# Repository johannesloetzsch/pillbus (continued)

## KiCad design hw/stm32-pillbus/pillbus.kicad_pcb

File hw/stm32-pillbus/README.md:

# PillBus

Simple and configurable bus controllers based on STM32.

## [STM32F103C8T6](https://www.lcsc.com/datasheet/lcsc_datasheet_2302211130_STMicroelectronics-STM32F103C8T6_C8734.pdf)

Different from `OtterPill`, a newer MCU is used:

* ARM Cortex-M3
* 2V~3.6V Operating Voltage Range
* 50mA max current consumption (Run mode, 72MHz, all peripherals enabled)
* 64KB Program FLASH Storage
* 20KB RAM
* max 72MHz, Internal Oscillator
* 35/37 GPIO Ports
* 2 SPI, 2 I²C, 3 USART, 1 USB 2.0 full-speed, 1 CAN
* 12bit ADC
* DMA

[MCU pinout](./pinout.md)

### Rust

Examples on similar MCUs

* [blinky-rust-nix](https://github.com/johannesloetzsch/blinky-rust-nix)
* [jamesmunns OtterPill-rs](https://github.com/jamesmunns/OtterPill-rs)
* [Tock OS](https://github.com/tock)
* [LinuxM3](http://www.linux-arm.org/LinuxKernel/LinuxM3)

## Peripherals

### [WS2812B RGB-LEDs](https://wmsc.lcsc.com/wmsc/upload/file/pdf/v2/lcsc/2406131538_XINGLIGHT-XL-5050RGBC-WS2812B-S_C22461793.pdf)

* -0.5-5.5 V Supply Voltage
* 3.0-7.0 V Logic input Voltage
* 12 mA RGB output Current

## [Power supply via USB](https://en.wikipedia.org/wiki/USB_hardware#Allowable_current_draw)

| USB Specification         | Current | Voltage | Configuration                               | usage                                      |
| ------------------------- | ------- | ------- | ------------------------------------------- | ------------------------------------------ |
| USB 2.0 Low-power device  | 100mA   | 5V      | default                                     | 1-2 MCU at max or 5 MCU at low consumption |
| USB 2.0 High-power device | 500mA   | 5V      | „Power Budgeting“ during device enumeration | 5 MCU at max + 16 RGB-LEDs                 |
| USB Battery Charging      | 1.5 A   | 5V      | charger detection algorithm                 | 5 MCU at max + 96 RGB-LEDs                 |
| USB TypeC Power Delivery  | 3.0 A   | 5V      | PD IC                                       | 5 MCU at max + ~200 RGB-LEDs               |

### [USB Battery Charging](https://usb.org/sites/default/files/BCv1.2_070312_0.zip)

`Portable Devices` „with a Good Battery“ are required to implement the charger detection algorithm defined at [Battery Charging Specification section 3.3.2](https://usb.org/sites/default/files/BCv1.2_070312_0.zip)

#### Primary Detection

`Portable Devices` (PD) are required to implement `Primary Detection` to distinguish between `Standard Downstream Port` (SDP) and different types of `Charging Ports` (`Charging Downstream Port` (SDP) or `, `Dedicated Charging Port` (DCP)).

`Dedicated Charging Ports` are identified by `RDCP_DAT <= 200 Ω` between D+ and D−. The `Portable Device` sets D+ and tests on D- if a similar voltage is detected. 

`Charging Downstream Ports` are allowed to identify by either one of two ways:
1. D- is set within `TCP_VDM_EN` of a disconnect and then unset within `TCP_VDM_DIS` of a connect.
2. D- is set exactly when `VDAT_REF < D+ < VLGC`

`Accessory charging adapters` (ACA) exist for `USB On-The-Go` and have an additional detection mechanism.

#### Secondary Detection

Secondary Detection can be used to distinguish between DCP and CDP. Portable Devices that are ready to be enumerated are allowed to bypass Secondary Detection. Secondary Detection identifies `Dedicated Charging Ports` by `RDCP_DAT <= 200 Ω` between D+ and D−. The `Portable Device` sets D- and tests on D+ if a similar voltage is detected.

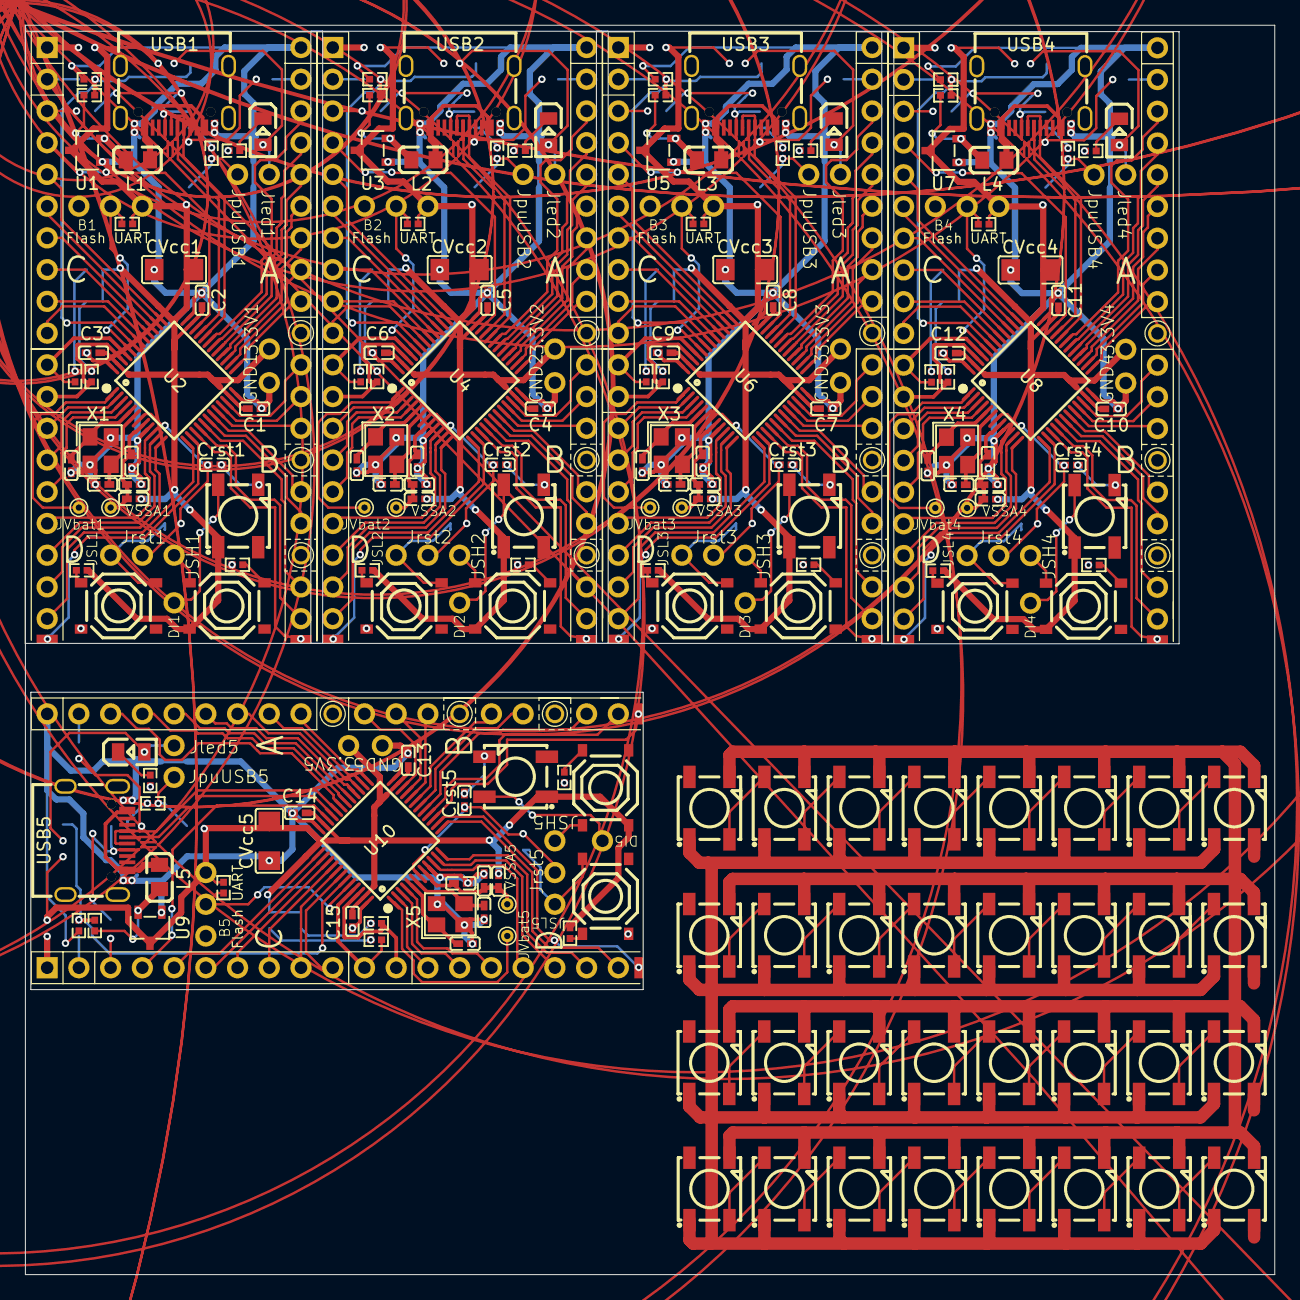
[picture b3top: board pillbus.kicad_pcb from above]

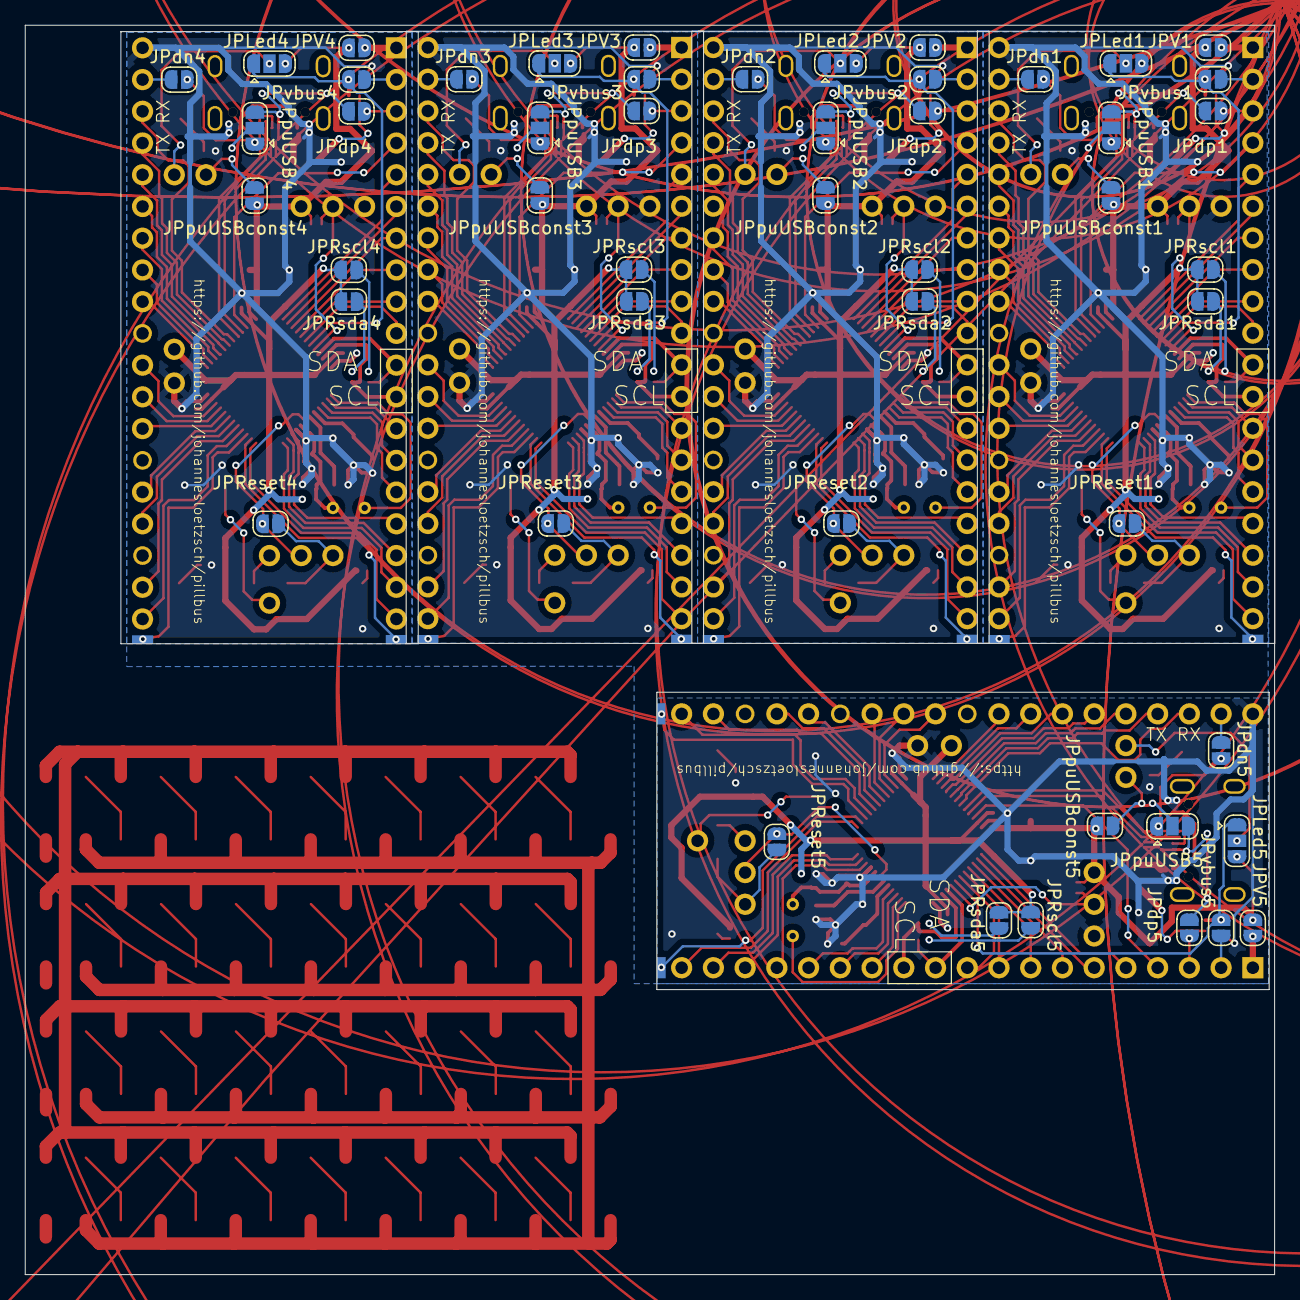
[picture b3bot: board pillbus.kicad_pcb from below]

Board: 2 copper layers, 100.0 x 100.0 mm, 297 parts (50 on the bottom side), 320 nets.

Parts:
3.3V1, 3.3V2, 3.3V3, 3.3V4, 3.3V5: PTH 1.7mm
B1, B2, B3, B4, B5: 3x PTH 1.7mm
C1, C2, C3, C4, C5, C6, C7, C8, C9, C10, C11, C12, C13, C14, C15: 100nF; C0402
CVcc1, CVcc2, CVcc3, CVcc4, CVcc5: 4.7uF; C1206
CVssA1, CVssA2, CVssA3, CVssA4, CVssA5: 1μF; C0402
CVssAn1, CVssAn2, CVssAn3, CVssAn4, CVssAn5: 10nF; C0402
Cosc1, Cosc2, Cosc3, Cosc4, Cosc5, Cosc6, Cosc7, Cosc8, Cosc9, Cosc10: 30pF; C0402
Crst1, Crst2, Crst3, Crst4, Crst5: 100nF; C0402
DI1, DI2, DI3, DI4, DI5: PTH 1.7mm
GND1, GND2, GND3, GND4, GND5: PTH 1.7mm
IDE_STM_A1, IDE_STM_A2, IDE_STM_A3, IDE_STM_A4, IDE_STM_A5: IDE STM A
IDE_STM_B1, IDE_STM_B2, IDE_STM_B3, IDE_STM_B4, IDE_STM_B5: IDE STM B cut
IDE_STM_C1, IDE_STM_C2, IDE_STM_C3, IDE_STM_C4, IDE_STM_C5: IDE STM C
IDE_STM_D1, IDE_STM_D2, IDE_STM_D3, IDE_STM_D4, IDE_STM_D5: IDE STM D cut
JPLed1, JPLed2, JPLed3, JPLed4, JPLed5: SolderJumper_3_Open; SolderJumper-3_P1.3mm_Open_RoundedPad1.0x1.5mm
JPReset1, JPReset2, JPReset3, JPReset4, JPReset5: SolderJumper_2_Open; SolderJumper-2_P1.3mm_Open_RoundedPad1.0x1.5mm
JPRscl1, JPRscl2, JPRscl3, JPRscl4, JPRscl5: SolderJumper_2_Open; SolderJumper-2_P1.3mm_Open_RoundedPad1.0x1.5mm
JPRsda1, JPRsda2, JPRsda3, JPRsda4, JPRsda5: SolderJumper_2_Open; SolderJumper-2_P1.3mm_Open_RoundedPad1.0x1.5mm
JPV1, JPV2, JPV3, JPV4, JPV5: SolderJumper_2_Open; SolderJumper-2_P1.3mm_Open_RoundedPad1.0x1.5mm
JPdn1, JPdn2, JPdn3, JPdn4, JPdn5: SolderJumper_2_Open; SolderJumper-2_P1.3mm_Open_RoundedPad1.0x1.5mm
JPdp1, JPdp2, JPdp3, JPdp4, JPdp5: SolderJumper_2_Open; SolderJumper-2_P1.3mm_Open_RoundedPad1.0x1.5mm
JPpuUSB1, JPpuUSB2, JPpuUSB3, JPpuUSB4, JPpuUSB5: SolderJumper_3_Open; SolderJumper-3_P1.3mm_Open_RoundedPad1.0x1.5mm
JPpuUSBconst1, JPpuUSBconst2, JPpuUSBconst3, JPpuUSBconst4, JPpuUSBconst5: SolderJumper_2_Open; SolderJumper-2_P1.3mm_Open_RoundedPad1.0x1.5mm
JPvbus1, JPvbus2, JPvbus3, JPvbus4, JPvbus5: SolderJumper_2_Open; SolderJumper-2_P1.3mm_Open_RoundedPad1.0x1.5mm
JSH1, JSH2, JSH3, JSH4, JSH5: PTH 1.7mm
JSL1, JSL2, JSL3, JSL4, JSL5: PTH 1.7mm
JVbat1, JVbat2, JVbat3, JVbat4, JVbat5: VBAT; TestPoint_THTPad_D1.0mm_Drill0.5mm
Jled1, Jled2, Jled3, Jled4, Jled5: PTH 1.7mm
JpuUSB1, JpuUSB2, JpuUSB3, JpuUSB4, JpuUSB5: PTH 1.7mm
Jrst1, Jrst2, Jrst3, Jrst4, Jrst5: PTH 1.7mm
L1, L2, L3, L4, L5: 100Ω@100MHz; L0805
LED1, LED2, LED3, LED4, LED5, LED6, LED7, LED8, LED9, LED10, LED11, LED12, LED13, LED14, LED15, LED16, LED17, LED18, LED19, LED20, LED21, LED22, LED23, LED24, LED25, LED26, LED27, LED28, LED29, LED30, LED31, LED32: WS2812B; LED-SMD_4P-L5.0-W5.0-TL-1
LED33, LED34, LED35, LED36, LED37: Green; LED0805-R-RD
LVssA1, LVssA2, LVssA3, LVssA4, LVssA5: 15-30nH; L0402
RGB1, RGB2, RGB3, RGB4, RGB5: LED WS2812B-S XL-5050RGBC; LED-SMD_4P-L5.0-W5.0-TL-1
RVbusI1, RVbusI2, RVbusI3, RVbusI4, RVbusI5: 51kΩ; R0402
RVbusO1, RVbusO2, RVbusO3, RVbusO4, RVbusO5: 100kΩ; R0402
Rled1, Rled2, Rled3, Rled4, Rled5: 1k-1.5k; R0402
Rpd1, Rpd2, Rpd3, Rpd4, Rpd5: 10kΩ; R0402
Rpu1, Rpu2, Rpu3, Rpu4, Rpu5: 10kΩ; R0402
RpuBoot1, RpuBoot2, RpuBoot3, RpuBoot4, RpuBoot5: 51kΩ; R0402
RpuUSB1, RpuUSB2, RpuUSB3, RpuUSB4, RpuUSB5: 1.5kΩ; R0402
Rscl1, Rscl2, Rscl3, Rscl4, Rscl5: 2.2kΩ; R0402
Rsda1, Rsda2, Rsda3, Rsda4, Rsda5: 2.2kΩ; R0402
SW1, SW2, SW3, SW4, SW5, SW6, SW7, SW8, SW9, SW10: Tactile Switch; SW-SMD_4P-L5.1-W5.1-P3.70-LS6.5-TL_H1.5
U1, U3, U5, U7, U9: 3.3V Voltage Regulator 200mA; SOT-23-3_L2.9-W1.6-P1.90-LS2.8-BR
U2, U4, U6, U8, U10: STM32F103C8T6; LQFP-48_L7.0-W7.0-P0.50-LS9.0-BL
USB1, USB2, USB3, USB4, USB5: USB_C; USB-C_SMD-TYPE-C-31-M-12
VSSA1, VSSA2, VSSA3, VSSA4, VSSA5: VSSA; TestPoint_THTPad_D1.0mm_Drill0.5mm
X1, X2, X3, X4, X5: Crystal 12MHz X322512MSB4SI; CRYSTAL-SMD_4P-L3.2-W2.5-BL

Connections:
+3.3V: 3.3V1.1, 3.3V2.1, 3.3V3.1, 3.3V4.1, 3.3V5.1, B1.3, B2.3, B3.3, B4.3, B5.3, C1.2, C2.2, C3.2, C4.2, C5.2, C6.2, C7.2, C8.2, C9.2, C10.2, C11.2, C12.2, C13.2, C14.2, C15.2, CVcc1.2, CVcc2.2, CVcc3.2, CVcc4.2, CVcc5.2, JPLed1.3 (B), JPLed2.3 (B), JPLed3.3 (B), JPLed4.3 (B), JPLed5.3 (B), JPRscl1.2 (B), JPRscl2.2 (B), JPRscl3.2 (B), JPRscl4.2 (B), JPRscl5.2 (B), JPRsda1.1 (A), JPRsda2.1 (A), JPRsda3.1 (A), JPRsda4.1 (A), JPRsda5.1 (A), JPV1.2 (B), JPV2.2 (B), JPV3.2 (B), JPV4.2 (B), JPV5.2 (B), JPpuUSBconst1.2 (B), JPpuUSBconst2.2 (B), JPpuUSBconst3.2 (B), JPpuUSBconst4.2 (B), JPpuUSBconst5.2 (B), LED1.1 (VDD), LED2.1 (VDD), LED3.1 (VDD), LED4.1 (VDD), LED5.1 (VDD), LED6.1 (VDD), LED7.1 (VDD), LED8.1 (VDD), LED9.1 (VDD), LED10.1 (VDD), LED11.1 (VDD), LED12.1 (VDD), LED13.1 (VDD), LED14.1 (VDD), LED15.1 (VDD), LED16.1 (VDD), LED17.1 (VDD), LED18.1 (VDD), LED19.1 (VDD), LED20.1 (VDD), LED21.1 (VDD), LED22.1 (VDD), LED23.1 (VDD), LED24.1 (VDD), LED25.1 (VDD), LED26.1 (VDD), LED27.1 (VDD), LED28.1 (VDD), LED29.1 (VDD), LED30.1 (VDD), LED31.1 (VDD), LED32.1 (VDD), LVssA1.2, LVssA2.2, LVssA3.2, LVssA4.2, LVssA5.2, RGB1.1 (VDD), RGB2.1 (VDD), RGB3.1 (VDD), RGB4.1 (VDD), RGB5.1 (VDD), Rpu1.2, Rpu2.2, Rpu3.2, Rpu4.2, Rpu5.2, RpuBoot1.1, RpuBoot2.1, RpuBoot3.1, RpuBoot4.1, RpuBoot5.1, SW2.2 (B), SW4.2 (B), SW6.2 (B), SW8.2 (B), SW10.2 (B), U1.3 (Vout), U2.23 (VSS_1), U2.35 (VSS_2), U2.47 (VSS_3), U3.3 (Vout), U4.23 (VSS_1), U4.35 (VSS_2), U4.47 (VSS_3), U5.3 (Vout), U6.23 (VSS_1), U6.35 (VSS_2), U6.47 (VSS_3), U7.3 (Vout), U8.23 (VSS_1), U8.35 (VSS_2), U8.47 (VSS_3), U9.3 (Vout), U10.23 (VSS_1), U10.35 (VSS_2), U10.47 (VSS_3)
/stm32pill1/Boot0: B2.2, RpuBoot2.2, U4.44 (BOOT0)
/stm32pill1/I2C1 SCL: IDE_STM_D2.SDA (IDE39_STM45), Rscl2.1, U4.45 (PB8)
/stm32pill1/I2C1 SDA: IDE_STM_D2.SCL (IDE37_STM46), Rsda2.1, U4.46 (PB9)
/stm32pill1/I2C2 SCL, USART3 TX: IDE_STM_B2.B1 (IDE24_STM13), U4.21 (PB10)
/stm32pill1/I2C2 SDA, USART3 RX: IDE_STM_B2.B0 (IDE22_STM14), U4.22 (PB11)
/stm32pill1/NRST: Crst2.2, JPReset2.1 (A), Jrst2.1, U4.7 (NRST)
/stm32pill1/OSC_IN: Cosc3.2, U4.5 (PD0-OSC_IN), X2.1 (OSC1)
/stm32pill1/OSC_OUT: Cosc4.2, U4.6 (PD1-OSC_OUT), X2.3 (OSC2)
/stm32pill1/SPI1 MISO: IDE_STM_B2.B6 (IDE38_STM3), U4.16 (PA6)
/stm32pill1/SPI1 MOSI: IDE_STM_B2.B5 (IDE36_STM4), U4.17 (PA7)
/stm32pill1/SPI1 SCK: IDE_STM_B2.B7 (IDE40_STM2), U4.15 (PA5)
/stm32pill1/SPI2 MISO: IDE_STM_A2.A5 (IDE14_STM17), U4.27 (PB14)
/stm32pill1/SPI2 MOSI: IDE_STM_A2.A4 (IDE12_STM18), U4.28 (PB15)
/stm32pill1/SPI2 NSS: IDE_STM_A2.A7 (IDE18_STM15), U4.25 (PB12)
/stm32pill1/SPI2 SCK: IDE_STM_A2.A6 (IDE16_STM16), U4.26 (PB13)
/stm32pill1/USART1 RX: IDE_STM_A2.A1 (IDE6_STM21), U4.31 (PA10)
/stm32pill1/USART1 TX: IDE_STM_A2.A2 (IDE8_STM20), U4.30 (PA9)
/stm32pill1/USB VBusSense: JPLed2.1 (A), JPvbus2.1 (A), RVbusI2.2, RVbusO2.1, U4.43 (PB7)
/stm32pill1/USBd+: JPdp2.2 (B), JPpuUSB2.3 (B), U4.33 (PA12), USB2.A6 (DP1), USB2.B6 (DP2)
/stm32pill1/USBd-: JPdn2.1 (A), JPpuUSB2.1 (A), U4.32 (PA11), USB2.A7 (DN1), USB2.B7 (DN2)
/stm32pill1/VBAT: JVbat2.1, U4.1 (VBAT)
/stm32pill1/VBUS: L2.1, RVbusI2.1, U3.2 (Vin)
/stm32pill1/VSSA: CVssA2.2, CVssAn2.2, LVssA2.1, U4.8 (VSSA), VSSA2.1
/stm32pill2/Boot0: B3.2, RpuBoot3.2, U6.44 (BOOT0)
/stm32pill2/I2C1 SCL: IDE_STM_D3.SDA (IDE39_STM45), Rscl3.1, U6.45 (PB8)
/stm32pill2/I2C1 SDA: IDE_STM_D3.SCL (IDE37_STM46), Rsda3.1, U6.46 (PB9)
/stm32pill2/I2C2 SCL, USART3 TX: IDE_STM_B3.B1 (IDE24_STM13), U6.21 (PB10)
/stm32pill2/I2C2 SDA, USART3 RX: IDE_STM_B3.B0 (IDE22_STM14), U6.22 (PB11)
/stm32pill2/NRST: Crst3.2, JPReset3.1 (A), Jrst3.1, U6.7 (NRST)
/stm32pill2/OSC_IN: Cosc5.2, U6.5 (PD0-OSC_IN), X3.1 (OSC1)
/stm32pill2/OSC_OUT: Cosc6.2, U6.6 (PD1-OSC_OUT), X3.3 (OSC2)
/stm32pill2/SPI1 MISO: IDE_STM_B3.B6 (IDE38_STM3), U6.16 (PA6)
/stm32pill2/SPI1 MOSI: IDE_STM_B3.B5 (IDE36_STM4), U6.17 (PA7)
/stm32pill2/SPI1 SCK: IDE_STM_B3.B7 (IDE40_STM2), U6.15 (PA5)
/stm32pill2/SPI2 MISO: IDE_STM_A3.A5 (IDE14_STM17), U6.27 (PB14)
/stm32pill2/SPI2 MOSI: IDE_STM_A3.A4 (IDE12_STM18), U6.28 (PB15)
/stm32pill2/SPI2 NSS: IDE_STM_A3.A7 (IDE18_STM15), U6.25 (PB12)
/stm32pill2/SPI2 SCK: IDE_STM_A3.A6 (IDE16_STM16), U6.26 (PB13)
/stm32pill2/USART1 RX: IDE_STM_A3.A1 (IDE6_STM21), U6.31 (PA10)
/stm32pill2/USART1 TX: IDE_STM_A3.A2 (IDE8_STM20), U6.30 (PA9)
/stm32pill2/USB VBusSense: JPLed3.1 (A), JPvbus3.1 (A), RVbusI3.2, RVbusO3.1, U6.43 (PB7)
/stm32pill2/USBd+: JPdp3.2 (B), JPpuUSB3.3 (B), U6.33 (PA12), USB3.A6 (DP1), USB3.B6 (DP2)
/stm32pill2/USBd-: JPdn3.1 (A), JPpuUSB3.1 (A), U6.32 (PA11), USB3.A7 (DN1), USB3.B7 (DN2)
/stm32pill2/VBAT: JVbat3.1, U6.1 (VBAT)
/stm32pill2/VBUS: L3.1, RVbusI3.1, U5.2 (Vin)
/stm32pill2/VSSA: CVssA3.2, CVssAn3.2, LVssA3.1, U6.8 (VSSA), VSSA3.1
/stm32pill3/Boot0: B4.2, RpuBoot4.2, U8.44 (BOOT0)
/stm32pill3/I2C1 SCL: IDE_STM_D4.SDA (IDE39_STM45), Rscl4.1, U8.45 (PB8)
/stm32pill3/I2C1 SDA: IDE_STM_D4.SCL (IDE37_STM46), Rsda4.1, U8.46 (PB9)
/stm32pill3/I2C2 SCL, USART3 TX: IDE_STM_B4.B1 (IDE24_STM13), U8.21 (PB10)
/stm32pill3/I2C2 SDA, USART3 RX: IDE_STM_B4.B0 (IDE22_STM14), U8.22 (PB11)
/stm32pill3/NRST: Crst4.2, JPReset4.1 (A), Jrst4.1, U8.7 (NRST)
/stm32pill3/OSC_IN: Cosc7.2, U8.5 (PD0-OSC_IN), X4.1 (OSC1)
/stm32pill3/OSC_OUT: Cosc8.2, U8.6 (PD1-OSC_OUT), X4.3 (OSC2)
/stm32pill3/SPI1 MISO: IDE_STM_B4.B6 (IDE38_STM3), U8.16 (PA6)
/stm32pill3/SPI1 MOSI: IDE_STM_B4.B5 (IDE36_STM4), U8.17 (PA7)
/stm32pill3/SPI1 SCK: IDE_STM_B4.B7 (IDE40_STM2), U8.15 (PA5)
/stm32pill3/SPI2 MISO: IDE_STM_A4.A5 (IDE14_STM17), U8.27 (PB14)
/stm32pill3/SPI2 MOSI: IDE_STM_A4.A4 (IDE12_STM18), U8.28 (PB15)
/stm32pill3/SPI2 NSS: IDE_STM_A4.A7 (IDE18_STM15), U8.25 (PB12)
/stm32pill3/SPI2 SCK: IDE_STM_A4.A6 (IDE16_STM16), U8.26 (PB13)
/stm32pill3/USART1 RX: IDE_STM_A4.A1 (IDE6_STM21), U8.31 (PA10)
/stm32pill3/USART1 TX: IDE_STM_A4.A2 (IDE8_STM20), U8.30 (PA9)
/stm32pill3/USB VBusSense: JPLed4.1 (A), JPvbus4.1 (A), RVbusI4.2, RVbusO4.1, U8.43 (PB7)
/stm32pill3/USBd+: JPdp4.2 (B), JPpuUSB4.3 (B), U8.33 (PA12), USB4.A6 (DP1), USB4.B6 (DP2)
/stm32pill3/USBd-: JPdn4.1 (A), JPpuUSB4.1 (A), U8.32 (PA11), USB4.A7 (DN1), USB4.B7 (DN2)
/stm32pill3/VBAT: JVbat4.1, U8.1 (VBAT)
/stm32pill3/VBUS: L4.1, RVbusI4.1, U7.2 (Vin)
/stm32pill3/VSSA: CVssA4.2, CVssAn4.2, LVssA4.1, U8.8 (VSSA), VSSA4.1
/stm32pill4/Boot0: B5.2, RpuBoot5.2, U10.44 (BOOT0)
/stm32pill4/I2C1 SCL: IDE_STM_D5.SDA (IDE39_STM45), Rscl5.1, U10.45 (PB8)
/stm32pill4/I2C1 SDA: IDE_STM_D5.SCL (IDE37_STM46), Rsda5.1, U10.46 (PB9)
/stm32pill4/I2C2 SCL, USART3 TX: IDE_STM_B5.B1 (IDE24_STM13), U10.21 (PB10)
/stm32pill4/I2C2 SDA, USART3 RX: IDE_STM_B5.B0 (IDE22_STM14), U10.22 (PB11)
/stm32pill4/NRST: Crst5.2, JPReset5.1 (A), Jrst5.1, U10.7 (NRST)
/stm32pill4/OSC_IN: Cosc9.2, U10.5 (PD0-OSC_IN), X5.1 (OSC1)
/stm32pill4/OSC_OUT: Cosc10.2, U10.6 (PD1-OSC_OUT), X5.3 (OSC2)
/stm32pill4/SPI1 MISO: IDE_STM_B5.B6 (IDE38_STM3), U10.16 (PA6)
/stm32pill4/SPI1 MOSI: IDE_STM_B5.B5 (IDE36_STM4), U10.17 (PA7)
/stm32pill4/SPI1 SCK: IDE_STM_B5.B7 (IDE40_STM2), U10.15 (PA5)
/stm32pill4/SPI2 MISO: IDE_STM_A5.A5 (IDE14_STM17), U10.27 (PB14)
/stm32pill4/SPI2 MOSI: IDE_STM_A5.A4 (IDE12_STM18), U10.28 (PB15)
/stm32pill4/SPI2 NSS: IDE_STM_A5.A7 (IDE18_STM15), U10.25 (PB12)
/stm32pill4/SPI2 SCK: IDE_STM_A5.A6 (IDE16_STM16), U10.26 (PB13)
/stm32pill4/USART1 RX: IDE_STM_A5.A1 (IDE6_STM21), U10.31 (PA10)
/stm32pill4/USART1 TX: IDE_STM_A5.A2 (IDE8_STM20), U10.30 (PA9)
/stm32pill4/USB VBusSense: JPLed5.1 (A), JPvbus5.1 (A), RVbusI5.2, RVbusO5.1, U10.43 (PB7)
/stm32pill4/USBd+: JPdp5.2 (B), JPpuUSB5.3 (B), U10.33 (PA12), USB5.A6 (DP1), USB5.B6 (DP2)
/stm32pill4/USBd-: JPdn5.1 (A), JPpuUSB5.1 (A), U10.32 (PA11), USB5.A7 (DN1), USB5.B7 (DN2)
/stm32pill4/VBAT: JVbat5.1, U10.1 (VBAT)
/stm32pill4/VBUS: L5.1, RVbusI5.1, U9.2 (Vin)
/stm32pill4/VSSA: CVssA5.2, CVssAn5.2, LVssA5.1, U10.8 (VSSA), VSSA5.1
/stm32pill/Boot0: B1.2, RpuBoot1.2, U2.44 (BOOT0)
/stm32pill/I2C1 SCL: IDE_STM_D1.SDA (IDE39_STM45), Rscl1.1, U2.45 (PB8)
/stm32pill/I2C1 SDA: IDE_STM_D1.SCL (IDE37_STM46), Rsda1.1, U2.46 (PB9)
/stm32pill/I2C2 SCL, USART3 TX: IDE_STM_B1.B1 (IDE24_STM13), U2.21 (PB10)
/stm32pill/I2C2 SDA, USART3 RX: IDE_STM_B1.B0 (IDE22_STM14), U2.22 (PB11)
/stm32pill/NRST: Crst1.2, JPReset1.1 (A), Jrst1.1, U2.7 (NRST)
/stm32pill/OSC_IN: Cosc1.2, U2.5 (PD0-OSC_IN), X1.1 (OSC1)
/stm32pill/OSC_OUT: Cosc2.2, U2.6 (PD1-OSC_OUT), X1.3 (OSC2)
/stm32pill/SPI1 MISO: IDE_STM_B1.B6 (IDE38_STM3), U2.16 (PA6)
/stm32pill/SPI1 MOSI: IDE_STM_B1.B5 (IDE36_STM4), U2.17 (PA7)
/stm32pill/SPI1 SCK: IDE_STM_B1.B7 (IDE40_STM2), U2.15 (PA5)
/stm32pill/SPI2 MISO: IDE_STM_A1.A5 (IDE14_STM17), U2.27 (PB14)
/stm32pill/SPI2 MOSI: IDE_STM_A1.A4 (IDE12_STM18), U2.28 (PB15)
/stm32pill/SPI2 NSS: IDE_STM_A1.A7 (IDE18_STM15), U2.25 (PB12)
/stm32pill/SPI2 SCK: IDE_STM_A1.A6 (IDE16_STM16), U2.26 (PB13)
/stm32pill/USART1 RX: IDE_STM_A1.A1 (IDE6_STM21), U2.31 (PA10)
/stm32pill/USART1 TX: IDE_STM_A1.A2 (IDE8_STM20), U2.30 (PA9)
/stm32pill/USB VBusSense: JPLed1.1 (A), JPvbus1.1 (A), RVbusI1.2, RVbusO1.1, U2.43 (PB7)
/stm32pill/USBd+: JPdp1.2 (B), JPpuUSB1.3 (B), U2.33 (PA12), USB1.A6 (DP1), USB1.B6 (DP2)
/stm32pill/USBd-: JPdn1.1 (A), JPpuUSB1.1 (A), U2.32 (PA11), USB1.A7 (DN1), USB1.B7 (DN2)
/stm32pill/VBAT: JVbat1.1, U2.1 (VBAT)
/stm32pill/VBUS: L1.1, RVbusI1.1, U1.2 (Vin)
/stm32pill/VSSA: CVssA1.2, CVssAn1.2, LVssA1.1, U2.8 (VSSA), VSSA1.1
GND: B1.1, B2.1, B3.1, B4.1, B5.1, C1.1, C2.1, C3.1, C4.1, C5.1, C6.1, C7.1, C8.1, C9.1, C10.1, C11.1, C12.1, C13.1, C14.1, C15.1, CVcc1.1, CVcc2.1, CVcc3.1, CVcc4.1, CVcc5.1, CVssA1.1, CVssA2.1, CVssA3.1, CVssA4.1, CVssA5.1, CVssAn1.1, CVssAn2.1, CVssAn3.1, CVssAn4.1, CVssAn5.1, Cosc1.1, Cosc2.1, Cosc3.1, Cosc4.1, Cosc5.1, Cosc6.1, Cosc7.1, Cosc8.1, Cosc9.1, Cosc10.1, Crst1.1, Crst2.1, Crst3.1, Crst4.1, Crst5.1, GND1.1, GND2.1, GND3.1, GND4.1, GND5.1, IDE_STM_A1.GND (IDE2_STM24), IDE_STM_A2.GND (IDE2_STM24), IDE_STM_A3.GND (IDE2_STM24), IDE_STM_A4.GND (IDE2_STM24), IDE_STM_A5.GND (IDE2_STM24), LED1.3 (GND), LED2.3 (GND), LED3.3 (GND), LED4.3 (GND), LED5.3 (GND), LED6.3 (GND), LED7.3 (GND), LED8.3 (GND), LED9.3 (GND), LED10.3 (GND), LED11.3 (GND), LED12.3 (GND), LED13.3 (GND), LED14.3 (GND), LED15.3 (GND), LED16.3 (GND), LED17.3 (GND), LED18.3 (GND), LED19.3 (GND), LED20.3 (GND), LED21.3 (GND), LED22.3 (GND), LED23.3 (GND), LED24.3 (GND), LED25.3 (GND), LED26.3 (GND), LED27.3 (GND), LED28.3 (GND), LED29.3 (GND), LED30.3 (GND), LED31.3 (GND), LED32.3 (GND), RGB1.3 (GND), RGB2.3 (GND), RGB3.3 (GND), RGB4.3 (GND), RGB5.3 (GND), RVbusO1.2, RVbusO2.2, RVbusO3.2, RVbusO4.2, RVbusO5.2, Rled1.1, Rled2.1, Rled3.1, Rled4.1, Rled5.1, Rpd1.1, Rpd2.1, Rpd3.1, Rpd4.1, Rpd5.1, SW1.3 (C), SW3.3 (C), SW5.3 (C), SW7.3 (C), SW9.3 (C), U1.1 (GND), U2.9 (VDDA), U2.24 (VDD_1), U2.36 (VDD_2), U2.48 (VDD_3), U3.1 (GND), U4.9 (VDDA), U4.24 (VDD_1), U4.36 (VDD_2), U4.48 (VDD_3), U5.1 (GND), U6.9 (VDDA), U6.24 (VDD_1), U6.36 (VDD_2), U6.48 (VDD_3), U7.1 (GND), U8.9 (VDDA), U8.24 (VDD_1), U8.36 (VDD_2), U8.48 (VDD_3), U9.1 (GND), U10.9 (VDDA), U10.24 (VDD_1), U10.36 (VDD_2), U10.48 (VDD_3), USB1.A1 (GND), USB1.A12 (GND), USB1.B1 (GND), USB1.B12 (GND), USB2.A1 (GND), USB2.A12 (GND), USB2.B1 (GND), USB2.B12 (GND), USB3.A1 (GND), USB3.A12 (GND), USB3.B1 (GND), USB3.B12 (GND), USB4.A1 (GND), USB4.A12 (GND), USB4.B1 (GND), USB4.B12 (GND), USB5.A1 (GND), USB5.A12 (GND), USB5.B1 (GND), USB5.B12 (GND), X1.2 (GND), X1.4 (GND), X2.2 (GND), X2.4 (GND), X3.2 (GND), X3.4 (GND), X4.2 (GND), X4.4 (GND), X5.2 (GND), X5.4 (GND)
unnamed: DI1.1, RGB1.4 (DI)
unnamed: DI2.1, RGB2.4 (DI)
unnamed: DI3.1, RGB3.4 (DI)
unnamed: DI4.1, RGB4.4 (DI)
unnamed: DI5.1, RGB5.4 (DI)
unnamed: IDE_STM_A1.A0 (IDE4_STM22), JPdn1.2 (B)
unnamed: IDE_STM_A1.A3 (IDE10_STM19), U2.29 (PA8)
unnamed: IDE_STM_A2.A0 (IDE4_STM22), JPdn2.2 (B)
unnamed: IDE_STM_A2.A3 (IDE10_STM19), U4.29 (PA8)
unnamed: IDE_STM_A3.A0 (IDE4_STM22), JPdn3.2 (B)
unnamed: IDE_STM_A3.A3 (IDE10_STM19), U6.29 (PA8)
unnamed: IDE_STM_A4.A0 (IDE4_STM22), JPdn4.2 (B)
unnamed: IDE_STM_A4.A3 (IDE10_STM19), U8.29 (PA8)
unnamed: IDE_STM_A5.A0 (IDE4_STM22), JPdn5.2 (B)
unnamed: IDE_STM_A5.A3 (IDE10_STM19), U10.29 (PA8)
unnamed: IDE_STM_B1.B2 (IDE26_STM12), U2.20 (PB2)
unnamed: IDE_STM_B1.B3 (IDE30_STM11), U2.19 (PB1)
unnamed: IDE_STM_B1.B4 (IDE32_STM10), U2.18 (PB0)
unnamed: IDE_STM_B2.B2 (IDE26_STM12), U4.20 (PB2)
unnamed: IDE_STM_B2.B3 (IDE30_STM11), U4.19 (PB1)
unnamed: IDE_STM_B2.B4 (IDE32_STM10), U4.18 (PB0)
unnamed: IDE_STM_B3.B2 (IDE26_STM12), U6.20 (PB2)
unnamed: IDE_STM_B3.B3 (IDE30_STM11), U6.19 (PB1)
unnamed: IDE_STM_B3.B4 (IDE32_STM10), U6.18 (PB0)
unnamed: IDE_STM_B4.B2 (IDE26_STM12), U8.20 (PB2)
unnamed: IDE_STM_B4.B3 (IDE30_STM11), U8.19 (PB1)
unnamed: IDE_STM_B4.B4 (IDE32_STM10), U8.18 (PB0)
unnamed: IDE_STM_B5.B2 (IDE26_STM12), U10.20 (PB2)
unnamed: IDE_STM_B5.B3 (IDE30_STM11), U10.19 (PB1)
unnamed: IDE_STM_B5.B4 (IDE32_STM10), U10.18 (PB0)
unnamed: IDE_STM_C1.3V3 (IDE1_STM23), JPV1.1 (A)
unnamed: IDE_STM_C1.VBusSense (IDE3_STM43), JPvbus1.2 (B)
unnamed: IDE_STM_C1.C0 (IDE5_STM25), JPdp1.1 (A)
unnamed: IDE_STM_C1.C1 (IDE7_STM26), U2.34 (PA13)
unnamed: IDE_STM_C1.C2 (IDE9_STM27), U2.37 (PA14)
unnamed: IDE_STM_C1.C3 (IDE11_STM28), U2.38 (PA15)
unnamed: IDE_STM_C1.C4 (IDE13_STM29), U2.39 (PB3)
unnamed: IDE_STM_C1.C5 (IDE15_STM30), U2.40 (PB4)
unnamed: IDE_STM_C1.C6 (IDE17_STM31), U2.41 (PB5)
unnamed: IDE_STM_C1.C7 (IDE19_STM32), U2.42 (PB6)
unnamed: IDE_STM_C2.3V3 (IDE1_STM23), JPV2.1 (A)
unnamed: IDE_STM_C2.VBusSense (IDE3_STM43), JPvbus2.2 (B)
unnamed: IDE_STM_C2.C0 (IDE5_STM25), JPdp2.1 (A)
unnamed: IDE_STM_C2.C1 (IDE7_STM26), U4.34 (PA13)
unnamed: IDE_STM_C2.C2 (IDE9_STM27), U4.37 (PA14)
unnamed: IDE_STM_C2.C3 (IDE11_STM28), U4.38 (PA15)
unnamed: IDE_STM_C2.C4 (IDE13_STM29), U4.39 (PB3)
unnamed: IDE_STM_C2.C5 (IDE15_STM30), U4.40 (PB4)
unnamed: IDE_STM_C2.C6 (IDE17_STM31), U4.41 (PB5)
unnamed: IDE_STM_C2.C7 (IDE19_STM32), U4.42 (PB6)
unnamed: IDE_STM_C3.3V3 (IDE1_STM23), JPV3.1 (A)
unnamed: IDE_STM_C3.VBusSense (IDE3_STM43), JPvbus3.2 (B)
unnamed: IDE_STM_C3.C0 (IDE5_STM25), JPdp3.1 (A)
unnamed: IDE_STM_C3.C1 (IDE7_STM26), U6.34 (PA13)
unnamed: IDE_STM_C3.C2 (IDE9_STM27), U6.37 (PA14)
unnamed: IDE_STM_C3.C3 (IDE11_STM28), U6.38 (PA15)
unnamed: IDE_STM_C3.C4 (IDE13_STM29), U6.39 (PB3)
unnamed: IDE_STM_C3.C5 (IDE15_STM30), U6.40 (PB4)
unnamed: IDE_STM_C3.C6 (IDE17_STM31), U6.41 (PB5)
unnamed: IDE_STM_C3.C7 (IDE19_STM32), U6.42 (PB6)
unnamed: IDE_STM_C4.3V3 (IDE1_STM23), JPV4.1 (A)
unnamed: IDE_STM_C4.VBusSense (IDE3_STM43), JPvbus4.2 (B)
unnamed: IDE_STM_C4.C0 (IDE5_STM25), JPdp4.1 (A)
unnamed: IDE_STM_C4.C1 (IDE7_STM26), U8.34 (PA13)
unnamed: IDE_STM_C4.C2 (IDE9_STM27), U8.37 (PA14)
unnamed: IDE_STM_C4.C3 (IDE11_STM28), U8.38 (PA15)
unnamed: IDE_STM_C4.C4 (IDE13_STM29), U8.39 (PB3)
unnamed: IDE_STM_C4.C5 (IDE15_STM30), U8.40 (PB4)
unnamed: IDE_STM_C4.C6 (IDE17_STM31), U8.41 (PB5)
unnamed: IDE_STM_C4.C7 (IDE19_STM32), U8.42 (PB6)
unnamed: IDE_STM_C5.3V3 (IDE1_STM23), JPV5.1 (A)
unnamed: IDE_STM_C5.VBusSense (IDE3_STM43), JPvbus5.2 (B)
unnamed: IDE_STM_C5.C0 (IDE5_STM25), JPdp5.1 (A)
unnamed: IDE_STM_C5.C1 (IDE7_STM26), U10.34 (PA13)
unnamed: IDE_STM_C5.C2 (IDE9_STM27), U10.37 (PA14)
unnamed: IDE_STM_C5.C3 (IDE11_STM28), U10.38 (PA15)
unnamed: IDE_STM_C5.C4 (IDE13_STM29), U10.39 (PB3)
unnamed: IDE_STM_C5.C5 (IDE15_STM30), U10.40 (PB4)
unnamed: IDE_STM_C5.C6 (IDE17_STM31), U10.41 (PB5)
unnamed: IDE_STM_C5.C7 (IDE19_STM32), U10.42 (PB6)
unnamed: IDE_STM_D1.D7 (IDE21_STM33), U2.14 (PA4)
unnamed: IDE_STM_D1.D6 (IDE23_STM34), U2.13 (PA3)
unnamed: IDE_STM_D1.D5 (IDE25_STM37), U2.12 (PA2)
unnamed: IDE_STM_D1.D4 (IDE27_STM38), U2.11 (PA1)
unnamed: IDE_STM_D1.D3 (IDE29_STM39), U2.10 (PA0-WKUP)
unnamed: IDE_STM_D1.D2 (IDE31_STM40), U2.4 (PC15-OSC32_OUT)
unnamed: IDE_STM_D1.D1 (IDE33_STM41), U2.3 (PC14-OSC32_IN)
unnamed: IDE_STM_D1.D0 (IDE35_STM42), U2.2 (PC13-TAMPER-RTC)
unnamed: IDE_STM_D2.D7 (IDE21_STM33), U4.14 (PA4)
unnamed: IDE_STM_D2.D6 (IDE23_STM34), U4.13 (PA3)
unnamed: IDE_STM_D2.D5 (IDE25_STM37), U4.12 (PA2)
unnamed: IDE_STM_D2.D4 (IDE27_STM38), U4.11 (PA1)
unnamed: IDE_STM_D2.D3 (IDE29_STM39), U4.10 (PA0-WKUP)
unnamed: IDE_STM_D2.D2 (IDE31_STM40), U4.4 (PC15-OSC32_OUT)
unnamed: IDE_STM_D2.D1 (IDE33_STM41), U4.3 (PC14-OSC32_IN)
unnamed: IDE_STM_D2.D0 (IDE35_STM42), U4.2 (PC13-TAMPER-RTC)
unnamed: IDE_STM_D3.D7 (IDE21_STM33), U6.14 (PA4)
unnamed: IDE_STM_D3.D6 (IDE23_STM34), U6.13 (PA3)
unnamed: IDE_STM_D3.D5 (IDE25_STM37), U6.12 (PA2)
unnamed: IDE_STM_D3.D4 (IDE27_STM38), U6.11 (PA1)
unnamed: IDE_STM_D3.D3 (IDE29_STM39), U6.10 (PA0-WKUP)
unnamed: IDE_STM_D3.D2 (IDE31_STM40), U6.4 (PC15-OSC32_OUT)
unnamed: IDE_STM_D3.D1 (IDE33_STM41), U6.3 (PC14-OSC32_IN)
unnamed: IDE_STM_D3.D0 (IDE35_STM42), U6.2 (PC13-TAMPER-RTC)
unnamed: IDE_STM_D4.D7 (IDE21_STM33), U8.14 (PA4)
unnamed: IDE_STM_D4.D6 (IDE23_STM34), U8.13 (PA3)
unnamed: IDE_STM_D4.D5 (IDE25_STM37), U8.12 (PA2)
unnamed: IDE_STM_D4.D4 (IDE27_STM38), U8.11 (PA1)
unnamed: IDE_STM_D4.D3 (IDE29_STM39), U8.10 (PA0-WKUP)
unnamed: IDE_STM_D4.D2 (IDE31_STM40), U8.4 (PC15-OSC32_OUT)
unnamed: IDE_STM_D4.D1 (IDE33_STM41), U8.3 (PC14-OSC32_IN)
unnamed: IDE_STM_D4.D0 (IDE35_STM42), U8.2 (PC13-TAMPER-RTC)
unnamed: IDE_STM_D5.D7 (IDE21_STM33), U10.14 (PA4)
unnamed: IDE_STM_D5.D6 (IDE23_STM34), U10.13 (PA3)
unnamed: IDE_STM_D5.D5 (IDE25_STM37), U10.12 (PA2)
unnamed: IDE_STM_D5.D4 (IDE27_STM38), U10.11 (PA1)
unnamed: IDE_STM_D5.D3 (IDE29_STM39), U10.10 (PA0-WKUP)
unnamed: IDE_STM_D5.D2 (IDE31_STM40), U10.4 (PC15-OSC32_OUT)
unnamed: IDE_STM_D5.D1 (IDE33_STM41), U10.3 (PC14-OSC32_IN)
unnamed: IDE_STM_D5.D0 (IDE35_STM42), U10.2 (PC13-TAMPER-RTC)
unnamed: JPLed1.2 (C), Jled1.1, LED33.1 (A)
unnamed: JPLed2.2 (C), Jled2.1, LED34.1 (A)
unnamed: JPLed3.2 (C), Jled3.1, LED35.1 (A)
unnamed: JPLed4.2 (C), Jled4.1, LED36.1 (A)
unnamed: JPLed5.2 (C), Jled5.1, LED37.1 (A)
unnamed: JPReset1.2 (B), JSL1.1, SW1.2 (B)
unnamed: JPReset2.2 (B), JSL2.1, SW3.2 (B)
unnamed: JPReset3.2 (B), JSL3.1, SW5.2 (B)
unnamed: JPReset4.2 (B), JSL4.1, SW7.2 (B)
unnamed: JPReset5.2 (B), JSL5.1, SW9.2 (B)
unnamed: JPRscl1.1 (A), Rscl1.2
unnamed: JPRscl2.1 (A), Rscl2.2
unnamed: JPRscl3.1 (A), Rscl3.2
unnamed: JPRscl4.1 (A), Rscl4.2
unnamed: JPRscl5.1 (A), Rscl5.2
unnamed: JPRsda1.2 (B), Rsda1.2
unnamed: JPRsda2.2 (B), Rsda2.2
unnamed: JPRsda3.2 (B), Rsda3.2
unnamed: JPRsda4.2 (B), Rsda4.2
unnamed: JPRsda5.2 (B), Rsda5.2
unnamed: JPpuUSB1.2 (C), RpuUSB1.1
unnamed: JPpuUSB2.2 (C), RpuUSB2.1
unnamed: JPpuUSB3.2 (C), RpuUSB3.1
unnamed: JPpuUSB4.2 (C), RpuUSB4.1
unnamed: JPpuUSB5.2 (C), RpuUSB5.1
unnamed: JPpuUSBconst1.1 (A), JpuUSB1.1, RpuUSB1.2
unnamed: JPpuUSBconst2.1 (A), JpuUSB2.1, RpuUSB2.2
unnamed: JPpuUSBconst3.1 (A), JpuUSB3.1, RpuUSB3.2
unnamed: JPpuUSBconst4.1 (A), JpuUSB4.1, RpuUSB4.2
unnamed: JPpuUSBconst5.1 (A), JpuUSB5.1, RpuUSB5.2
unnamed: JSH1.1, SW2.4 (D)
unnamed: JSH2.1, SW4.4 (D)
unnamed: JSH3.1, SW6.4 (D)
unnamed: JSH4.1, SW8.4 (D)
unnamed: JSH5.1, SW10.4 (D)
unnamed: L1.2, USB1.A4 (VBUS), USB1.A9 (VBUS), USB1.B4 (VBUS), USB1.B9 (VBUS)
unnamed: L2.2, USB2.A4 (VBUS), USB2.A9 (VBUS), USB2.B4 (VBUS), USB2.B9 (VBUS)
unnamed: L3.2, USB3.A4 (VBUS), USB3.A9 (VBUS), USB3.B4 (VBUS), USB3.B9 (VBUS)
unnamed: L4.2, USB4.A4 (VBUS), USB4.A9 (VBUS), USB4.B4 (VBUS), USB4.B9 (VBUS)
unnamed: L5.2, USB5.A4 (VBUS), USB5.A9 (VBUS), USB5.B4 (VBUS), USB5.B9 (VBUS)
unnamed: LED1.2 (DO), LED2.4 (DI)
unnamed: LED2.2 (DO), LED3.4 (DI)
unnamed: LED3.2 (DO), LED4.4 (DI)
unnamed: LED4.2 (DO), LED5.4 (DI)
unnamed: LED5.2 (DO), LED6.4 (DI)
unnamed: LED6.2 (DO), LED7.4 (DI)
unnamed: LED7.2 (DO), LED8.4 (DI)
unnamed: LED9.2 (DO), LED10.4 (DI)
unnamed: LED10.2 (DO), LED11.4 (DI)
unnamed: LED11.2 (DO), LED12.4 (DI)
unnamed: LED12.2 (DO), LED13.4 (DI)
unnamed: LED13.2 (DO), LED14.4 (DI)
unnamed: LED14.2 (DO), LED15.4 (DI)
unnamed: LED15.2 (DO), LED16.4 (DI)
unnamed: LED17.2 (DO), LED18.4 (DI)
unnamed: LED18.2 (DO), LED19.4 (DI)
unnamed: LED19.2 (DO), LED20.4 (DI)
unnamed: LED20.2 (DO), LED21.4 (DI)
unnamed: LED21.2 (DO), LED22.4 (DI)
unnamed: LED22.2 (DO), LED23.4 (DI)
unnamed: LED23.2 (DO), LED24.4 (DI)
unnamed: LED25.2 (DO), LED26.4 (DI)
unnamed: LED26.2 (DO), LED27.4 (DI)
unnamed: LED27.2 (DO), LED28.4 (DI)
unnamed: LED28.2 (DO), LED29.4 (DI)
unnamed: LED29.2 (DO), LED30.4 (DI)
unnamed: LED30.2 (DO), LED31.4 (DI)
unnamed: LED31.2 (DO), LED32.4 (DI)
unnamed: LED33.2 (K), Rled1.2
unnamed: LED34.2 (K), Rled2.2
unnamed: LED35.2 (K), Rled3.2
unnamed: LED36.2 (K), Rled4.2
unnamed: LED37.2 (K), Rled5.2
unnamed: Rpu1.1, SW1.1 (A)
unnamed: Rpd1.2, SW2.3 (C)
unnamed: Rpu2.1, SW3.1 (A)
unnamed: Rpd2.2, SW4.3 (C)
unnamed: Rpu3.1, SW5.1 (A)
unnamed: Rpd3.2, SW6.3 (C)
unnamed: Rpu4.1, SW7.1 (A)
unnamed: Rpd4.2, SW8.3 (C)
unnamed: Rpu5.1, SW9.1 (A)
unnamed: Rpd5.2, SW10.3 (C)

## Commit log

2024-11-08 hierachical schematic+pcb
2024-11-10 stm32pill schema
2024-11-11 kicad-libs/ribbon
2024-11-13 ide stm
2024-11-17 stm32pill pcb
2024-11-19 stm32-panel
2024-11-20 added capacitor at volatage regulator input
2024-11-21 improved layout
2024-11-21 annotations
2024-11-22 changed layout of bus board
2024-11-22 order v0.1.0
2024-11-22 boot0: pullDown + serial resistor
2024-12-16 panel
